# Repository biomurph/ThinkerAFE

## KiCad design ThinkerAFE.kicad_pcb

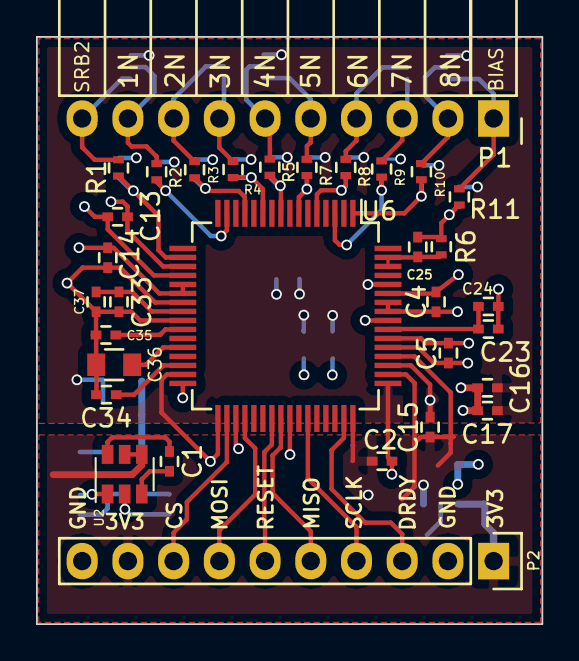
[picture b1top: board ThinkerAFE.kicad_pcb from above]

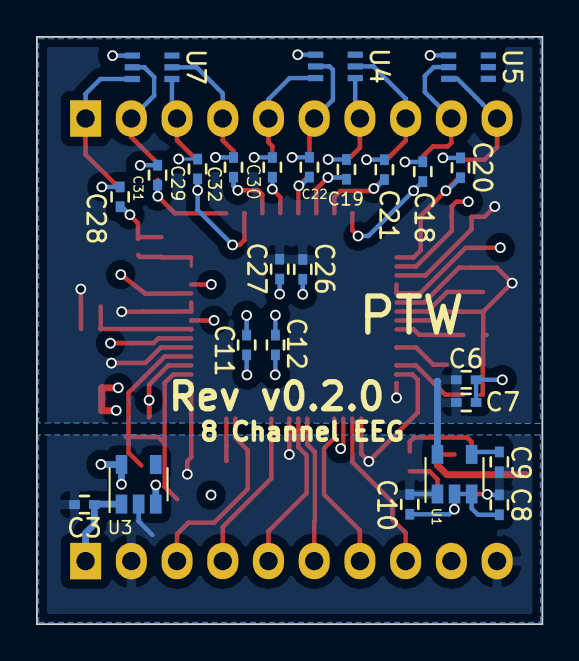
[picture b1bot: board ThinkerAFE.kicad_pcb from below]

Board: 4 copper layers, 28.1 x 32.6 mm, 57 parts (25 on the bottom side), 40 nets.

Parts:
C1, C7, C10, C17, C33: 10uF; C_0402
C2, C4, C11, C13, C24, C26, C27, C34, C35: 1uF; C_0402
C3, C5, C12, C14, C23, C37: 0.1uF; C_0402
C6, C8, C15, C16: 2.2uF; C_0402
C9, C18, C19, C20, C21, C22, C28, C29, C30, C31, C32: 0.01uF; C_0402
C25: 1nF; C_0402
C36: 100uF; C_0805
P1: CONN_01X10; Socket_Strip_Angled_1x10
P2: CONN_01X10; Socket_Strip_Straight_1x10
R1, R2, R3, R4, R5, R7, R8, R9, R10, R11: 2.2k; R_0402
R6: 1M; R_0402
U1: TPS72325; SOT-23-5
U2: LM2664; SOT-23-6
U3: TLV70025DDC; SOT-23-5
U4, U5, U7: TPD4E1B06; SC70
U6: ADS1299; TQFP-64_10x10mm_Pitch0.5mm

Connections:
/1N: P1.9, R2.2, U5.2
/2N: P1.8, R3.2, U4.5
/3N: P1.7, R4.2, U4.4
/4N: P1.6, R5.2, U4.2
/5N: P1.5, R7.2, U4.1
/6N: P1.4, R8.2, U7.5
/7N: P1.3, R9.2, U7.4
/8N: P1.2, R10.2, U7.2
/-RAW: C8.1, C10.1, U1.2, U1.3, U2.2
/BIAS: P1.1, R11.2, U7.1
/BIAS_DRV: C25.1, C28.1, R6.1, R11.1
/CS: P2.6, U6.39
/DRDY: P2.3, U6.47
/IN1N: C18.2, R2.1, U6.15
/IN2N: C21.2, R3.1, U6.13
/IN3N: C19.2, R4.1, U6.11
/IN4N: C22.2, R5.1, U6.9
/IN5N: C30.1, R7.1, U6.7
/IN6N: C32.1, R8.1, U6.5
/IN7N: C29.1, R9.1, U6.3
/IN8N: C31.1, R10.1, U6.1
/INSRB2: C20.2, R1.1, U6.18
/MISO: P2.4, U6.43
/MOSI: P2.8, U6.34
/RESET: P2.7, U6.36
/SCLK: P2.5, U6.40
/SRB2: P1.10, R1.2, U5.1
GNDA: C2.2, C3.2, C6.2, C7.2, C8.2, C9.2, C10.2, C11.2, C12.2, C15.2, C16.2, C17.2, C18.1, C19.1, C20.1, C21.1, C22.1, C26.2, C27.2, C28.2, C29.2, C30.2, C31.2, C32.2, P2.2, P2.10, U1.1, U2.1, U3.2, U4.3, U5.3, U6.31, U6.33, U6.41, U6.49, U6.51, U6.60, U7.3
unnamed: C1.1, U2.6
unnamed: C1.2, U2.3
unnamed: C9.1, U1.4
unnamed: C23.2, C24.2, U6.55
unnamed: C25.2, R6.2, U6.62, U6.63
unnamed: C33.2, C37.2, U6.24
unnamed: C34.1, U6.30
unnamed: C35.1, U6.26
unnamed: C36.1, U6.28
VDD: C2.1, C3.1, C15.1, P2.1, P2.9, U2.4, U2.5, U3.1, U3.3, U6.35, U6.48, U6.50, U6.52
VDDA: C4.1, C5.1, C11.1, C12.1, C13.1, C14.1, C16.1, C17.1, U3.5, U6.19, U6.21, U6.22, U6.54, U6.56, U6.59
VSSA: C4.2, C5.2, C6.1, C7.1, C13.2, C14.2, C23.1, C24.1, C26.1, C27.1, C33.1, C34.2, C35.2, C36.2, C37.1, U1.5, U6.20, U6.23, U6.25, U6.32, U6.53, U6.57, U6.58

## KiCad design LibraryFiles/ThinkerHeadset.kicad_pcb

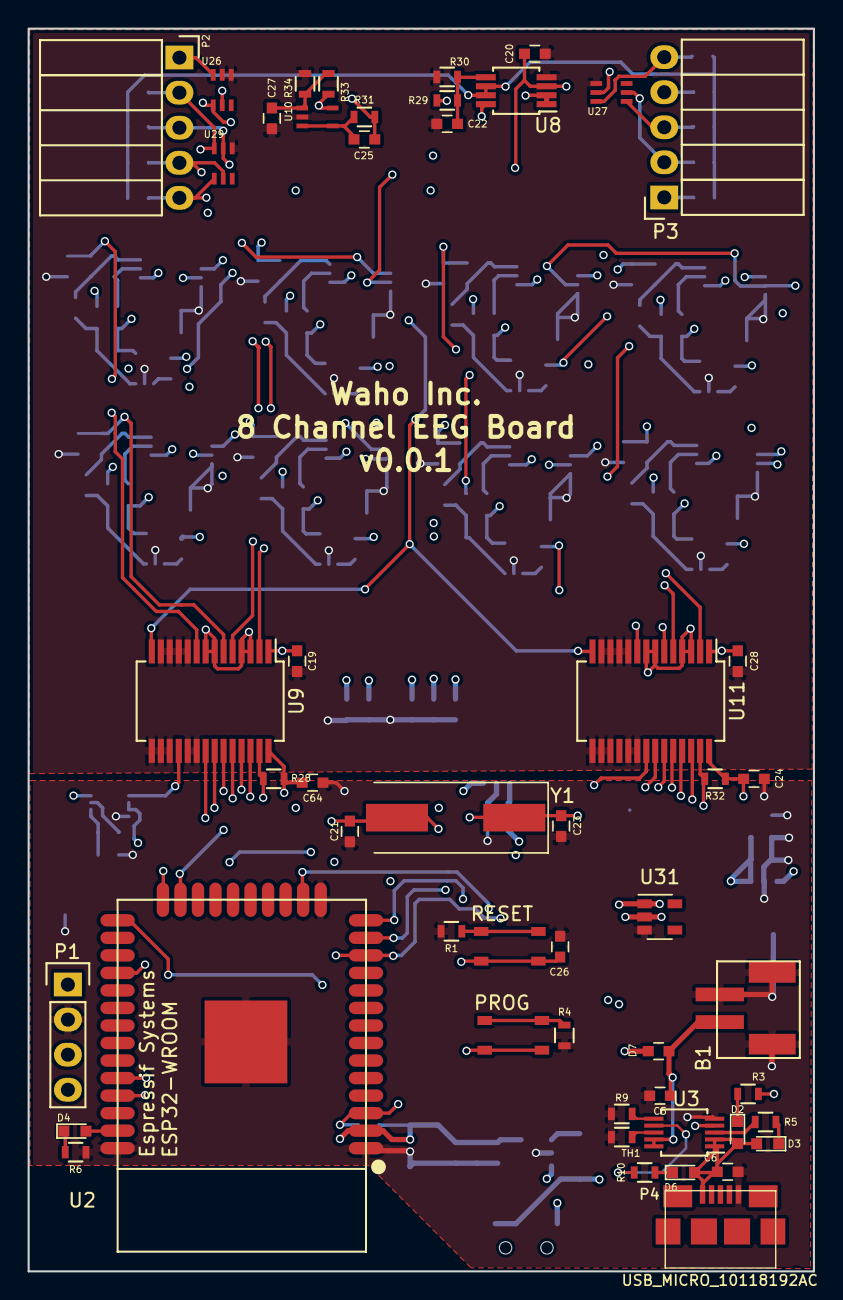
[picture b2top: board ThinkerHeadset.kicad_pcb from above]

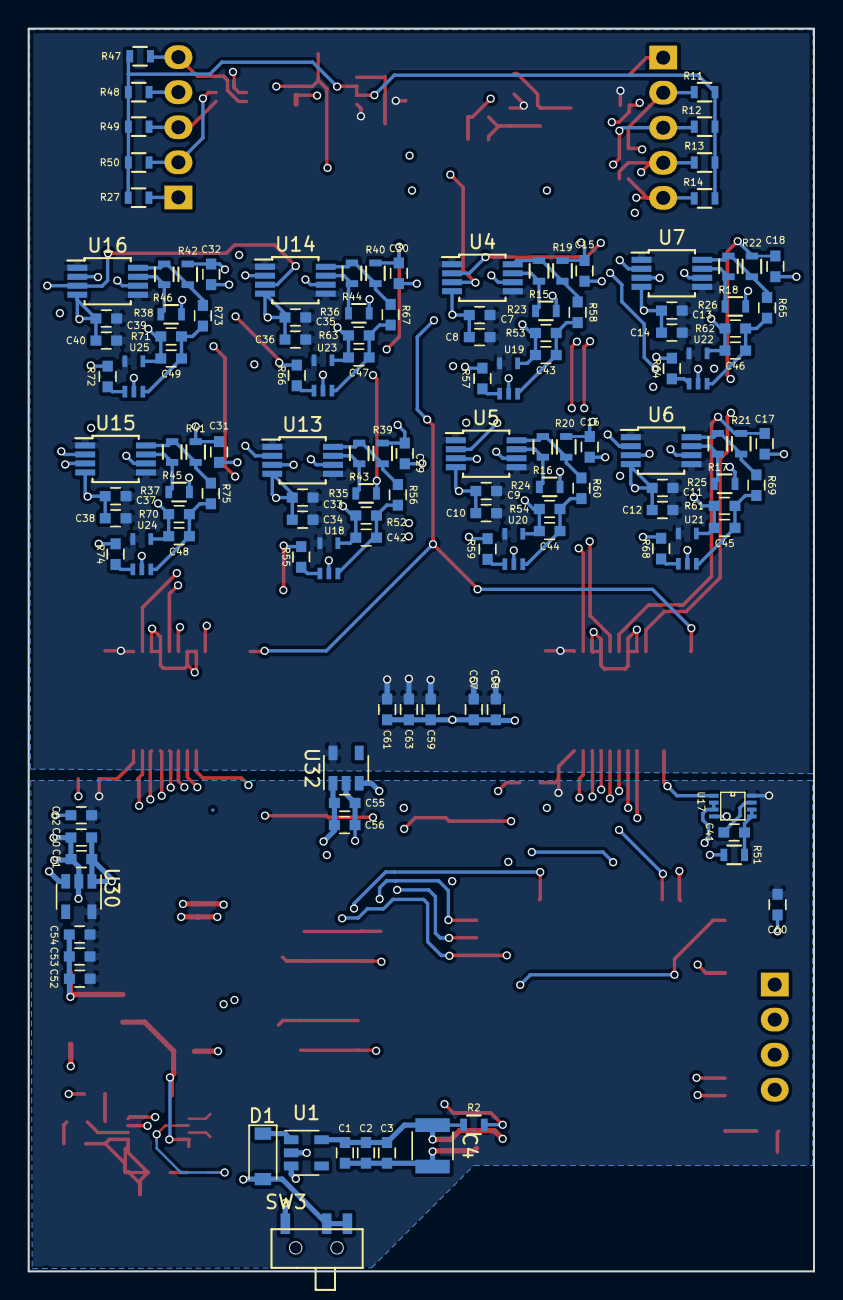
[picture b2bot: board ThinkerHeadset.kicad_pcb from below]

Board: 4 copper layers, 56.9 x 90.0 mm, 183 parts (132 on the bottom side), 102 nets.

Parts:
B1: JS_2_Battery; JST_RA_SMT
C1, C7, C8, C9, C10, C11, C12, C13, C14, C19, C20, C24, C28, C33, C34, C35, C36, C37, C38, C39, C40, C51, C52, C56, C57, C59, C60, C64: 0.1uF; C_0603
C2, C15, C16, C17, C18, C22, C25, C27, C29, C30, C31, C32, C50, C53, C55, C58, C61, C62: 1uF; C_0603
C3, C5, C6, C54, C63: 10uF; C_0603
C4: 100uF; C_1210
C21, C23: 18pF; C_0603
C26: 1nF; C_0603
C41: 0.01uF; C_0603
C42, C43, C44, C45, C46, C47, C48, C49: 3.3uF; C_0603
D1: MBR120; D_SOD-123
D2: LED-DONE; LED_0603
D3: LED-CRG; LED_0603
D4: LED; LED_0603
D6: RED; LED_0603
D7: D_Schottky; C_0603
P1: ESP_PROG; Socket_Strip_Straight_1x04
P2, P3: CONN_01X05; Socket_Strip_Angled_1x05
P4: USB_MICRO_10118192AC; MICRO-B_USB
PROG: ESP_PROG_SW; PTS810
R1, R4: 50; R_0603
R2: 12K; R_0603
R3, R5, R9, R10, R19, R20, R21, R22, R39, R40, R41, R42: 1K; R_0603
R6: 10K; R_0603
R11, R12, R13, R14, R27, R31, R47, R48, R49, R50: 330K; R_0603
R15, R16, R17, R18, R28, R29, R30, R32, R33, R34, R43, R44, R45, R46, R51: 100K; R_0603
R23, R24, R25, R26, R35, R36, R37, R38: 2K; R_0603
R52, R53, R54, R56, R58, R60, R61, R62, R63, R65, R67, R69, R70, R71, R73, R75: 1M; C_0603
R55, R57, R59, R64, R66, R68, R72, R74: 500K; C_0603
RESET: RESET_SW; PTS810
SW3: SPDT; SSSS810701SSSS810701
TH1: 10K/THERMISTOR; R_0603
U1: AP2112; SOT-23-5
U2: ESP32-WROOM
U3: MCP73833; MSOP-10_3x3mm_Pitch0.5mm
U4, U5, U6, U7, U13, U14, U15, U16: AD8237; MSOP-8_3x3mm_Pitch0.65mm
U8: LM7332; MSOP-8_3x3mm_Pitch0.65mm
U9, U11: MCP3912; SSOP-28_5.3x10.2mm_Pitch0.65mm
U10, U18, U19, U20, U21, U22, U23, U24, U25: MCP6V31U; SC-70-5
U17: 74LVC2G00; VSSOP-8
U26, U27, U29: TPD4E1B06; SC70
U30, U32: NCP551; SOT-23-5
U31: NCP300; SOT-23-5
Y1: Crystal_Small; Crystal_SMD_HC49-SD

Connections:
1_IN: P2.2, R11.1, U4.2, U29.1
2_IN: P2.3, R12.1, U5.2, U29.2
3_IN: P2.4, R13.1, U6.2, U29.5
4_IN: P2.5, R14.1, U7.2, U29.4
5_IN: P3.5, R47.1, U13.2, U27.1
6_IN: P3.4, R48.1, U14.2, U27.2
7_IN: P3.3, R49.1, U15.2, U27.4
8_IN: P3.2, R50.1, U16.2, U27.5
+3V3: C1.1, C2.1, C3.1, C4.1, P1.1, R2.1, U1.5, U2.2
+5V: C6.1, D2.2, D3.2, D6.2, P4.1, U3.1, U3.2
/AFE_Ganglion/REFIN+: C20.1, U8.3, U9.14, U11.14
/RX_ESP: P1.4, U2.34
/TX_ESP: P1.3, U2.35
DRDY: U2.28, U17.2, U17.3
D_G: C25.2, P2.1, R31.2, U26.1
GNDA: B1.2, B1.3, B1.4, C1.2, C2.2, C3.2, C4.2, C5.2, C6.2, C7.2, C8.2, C9.2, C10.2, C11.2, C12.2, C13.2, C14.2, C15.1, C16.2, C17.2, C18.2, C19.1, C20.2, C21.1, C22.2, C23.1, C24.1, C26.2, C27.2, C28.1, C29.1, C30.2, C31.2, C32.2, C33.2, C34.2, C35.2, C36.2, C37.2, C38.2, C39.2, C40.2, C50.1, C51.1, C52.1, C53.1, C54.1, C55.1, C56.1, C57.2, C58.2, C59.1, C60.2, C61.1, C62.2, C63.1, C64.1, P1.2, P4.5, R1.2, R4.2, R6.1, R9.2, R30.2, R34.2, R51.2, TH1.2, U1.2, U2.1, U2.15, U2.38, U2.39, U3.5, U4.4, U5.4, U6.4, U7.4, U8.4, U9.10, U9.11, U9.12, U9.13, U9.15, U9.16, U9.17, U9.19, U9.20, U10.2, U11.10, U11.11, U11.12, U11.13, U11.15, U11.16, U11.17, U11.19, U11.20, U13.4, U14.4, U15.4, U16.4, U17.4, U18.2, U19.2, U20.2, U21.2, U22.2, U23.2, U24.2, U25.2, U26.2, U26.3, U27.3, U29.3, U30.2, U31.3, U32.2
I_BIAS: R11.2, R12.2, R13.2, R14.2, R27.1, R47.2, R48.2, R49.2, R50.2, U8.6, U8.7
MCP1_SS: U2.23, U9.23
MCP2_SS: U2.24, U11.23
MCP_DRDY: U9.18, U17.1
MCP_RST: R28.2, R32.2, U2.12, U9.27, U11.27
MISO: U2.14, U9.25, U11.25
MOSI: U2.16, U9.26, U11.26
unnamed: C15.2, R19.1, U9.2
unnamed: C16.1, R20.1, U9.5
unnamed: C17.1, R21.1, U9.6
unnamed: C18.1, R22.1, U9.9
unnamed: C21.2, U9.21, U11.21, Y1.2
unnamed: C22.1, R29.2, R30.1, U8.5
unnamed: C23.2, U9.22, U11.22, Y1.1
unnamed: C25.1, R31.1, U10.3, U10.4
unnamed: C26.1, R2.2, RESET.3, RESET.4, U2.3
unnamed: C27.1, R33.2, R34.1, U10.1
unnamed: C29.2, R39.1, U11.2
unnamed: C30.1, R40.1, U11.5
unnamed: C31.1, R41.1, U11.6
unnamed: C32.1, R42.1, U11.9
unnamed: C41.1, U17.7
unnamed: C41.2, R51.1, U17.5, U17.6
unnamed: C42.1, R52.1, R56.2, U18.3
unnamed: C43.1, R53.1, R58.2, U19.3
unnamed: C44.1, R54.1, R60.2, U20.3
unnamed: C45.1, R61.1, R69.2, U21.3
unnamed: C46.1, R62.1, R65.2, U22.3
unnamed: C47.1, R63.1, R67.2, U23.3
unnamed: C48.1, R70.1, R75.2, U24.3
unnamed: C49.1, R71.1, R73.2, U25.3
unnamed: D1.1, U1.1
unnamed: D2.1, R3.1
unnamed: D3.1, R5.1
unnamed: D4.1, R6.2
unnamed: D4.2, U2.37
unnamed: D6.1, R10.1
unnamed: R1.1, RESET.1, RESET.2
unnamed: R3.2, U3.4
unnamed: PROG.1, PROG.2, R4.1
unnamed: R5.2, U3.3
unnamed: R9.1, U3.6
unnamed: R10.2, U3.7
unnamed: R15.1, R23.1, U4.7
unnamed: R16.1, R24.1, U5.7
unnamed: R17.1, R25.2, U6.7
unnamed: R18.1, R26.2, U7.7
unnamed: R35.1, R43.1, U13.7
unnamed: R36.1, R44.1, U14.7
unnamed: R37.2, R45.1, U15.7
unnamed: R38.2, R46.1, U16.7
unnamed: R55.2, U18.1
unnamed: R57.2, U19.1
unnamed: R59.2, U20.1
unnamed: R64.2, U22.1
unnamed: R66.2, U23.1
unnamed: R68.2, U21.1
unnamed: R72.2, U25.1
unnamed: R74.2, U24.1
unnamed: PROG.3, PROG.4, U2.25
unnamed: TH1.1, U3.8
OUT_1: R15.2, R19.2, R58.1, U4.8
OUT_2: R16.2, R20.2, R60.1, U5.8
OUT_3: R17.2, R21.2, R69.1, U6.8
OUT_4: R18.2, R22.2, R65.1, U7.8
OUT_5: R39.2, R43.2, R56.1, U13.8
OUT_6: R40.2, R44.2, R67.1, U14.8
OUT_7: R41.2, R45.2, R75.1, U15.8
OUT_8: R42.2, R46.2, R73.1, U16.8
RAW: B1.1, C5.1, D7.2, U3.9, U3.10
REF: P3.1, R27.2, U4.3, U5.3, U6.3, U7.3, U13.3, U14.3, U15.3, U16.3, U26.4
REF_1: C43.2, R53.2, U4.6, U19.4
REF_2: C44.2, R54.2, U5.6, U20.4
REF_3: C45.2, R61.2, U6.6, U21.4
REF_4: C46.2, R62.2, U7.6, U22.4
REF_5: C42.2, R52.2, U13.6, U18.4
REF_6: C47.2, R63.2, U14.6, U23.4
REF_7: C48.2, R70.2, U15.6, U24.4
REF_8: C49.2, R71.2, U16.6, U25.4
SCK: U2.13, U9.24, U11.24
VAA: C7.1, C8.1, C9.1, C10.1, C11.1, C12.1, C13.1, C14.1, C19.2, C28.2, C33.1, C34.1, C35.1, C36.1, C37.1, C38.1, C39.1, C40.1, C57.1, C58.1, C59.2, C61.2, C63.2, R29.1, R33.1, U4.1, U4.5, U5.1, U5.5, U6.1, U6.5, U7.1, U7.5, U8.8, U9.1, U10.5, U11.1, U13.1, U13.5, U14.1, U14.5, U15.1, U15.5, U16.1, U16.5, U18.5, U19.5, U20.5, U21.5, U22.5, U23.5, U24.5, U25.5, U26.5, U32.5
VDD: C24.2, C52.2, C53.2, C54.2, C60.1, C62.1, C64.2, R28.1, R32.1, U9.28, U11.28, U17.8, U30.5
V_BATT: D1.2, D7.1, SW3.2, SW3.3
V_ENABLE: U1.3, U30.3, U31.1, U32.3
V_IN: C50.2, C51.2, C55.2, C56.2, SW3.1, U30.1, U31.2, U32.1
V_REF: R23.2, R24.2, R25.1, R26.1, R35.2, R36.2, R37.1, R38.1, R55.1, R57.1, R59.1, R64.1, R66.1, R68.1, R72.1, R74.1, U8.1, U8.2, U9.3, U9.4, U9.7, U9.8, U11.3, U11.4, U11.7, U11.8

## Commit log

2017-05-08 Add components for AFE
2017-05-08 About ready to layout
2017-05-08 Placing parts
2017-05-09 laying board out
2017-05-09 Laying out the board
2017-05-09 Finished laying out board
2017-05-09 Finished layout, ready for prototyping
2017-05-09 saving
2017-05-09 finished new layout
2017-05-09 added text
2017-05-10 Done
2017-06-10 Move silk
2017-06-10 Update sch
2017-06-10 Lots of progress with 0.1.0
2017-06-11 Lots of progress
2017-06-11 Done with 0.2.0 layout and design
2017-08-15 FIX: Moved library dependecies to local folder
2017-08-25 Notes
2017-08-25 notes
    Solved it
